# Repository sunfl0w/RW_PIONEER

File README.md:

# RW-Pioneer

RW-Pioneer is a computer project inspired by Ben Eater's [8-bit breadboard computer project](https://www.youtube.com/playlist?list=PLowKtXNTBypGqImE405J2565dvjafglHU) over at YouTube.
I always wanted to build my own crappy computer, and the Pioneer was my first such attempt.
The design is not perfect by any means, but it was the best one I could come up with after a few semesters of studying computer science.

**Note that the RW-Pioneer is a few years old by now and I only compiled old schematics, layouts and code for this repository.**
**I recently added a binary compatible Verilog model of the system with Verilator test suite and Vivado project files for the Nexys A7 board.**

## Content

This repository contains the following schematics and software components:

- RW-Pioneer schematics, paper explaining the architecture and KiCad design files (Schematic and RW_PIONEER_WHITEPAPER.pdf)
- RW-Pioneer Verilog model with Verilator test suite and Vivado project files for the NEXYS A7 board (VerilogModel)
- HEX-Module and 1602-Module schematics and KiCad design files (ExpansionModules)
- Instruction LUT generator for the instruction decoder memory IC of the system (InstructionLUTGenerator)
- Memory-Programmer host and programmer software sources, schematics and KiCad design files (MemoryProgrammer)
- Simple software emulator for the system (RWEMU)

## Licenses

The software and schematics are licensed under the permissive BSD 3-Clause License.

## Links

[Visit my personal website to see the Pioneer in action.](https://www.rechenwerke.com/projects/rw_pioneer)

## Gallery

Image of a prototype board I assembled a few years ago.

Image of the NEXYS A7 board running the RW-Pioneer Verilog model.

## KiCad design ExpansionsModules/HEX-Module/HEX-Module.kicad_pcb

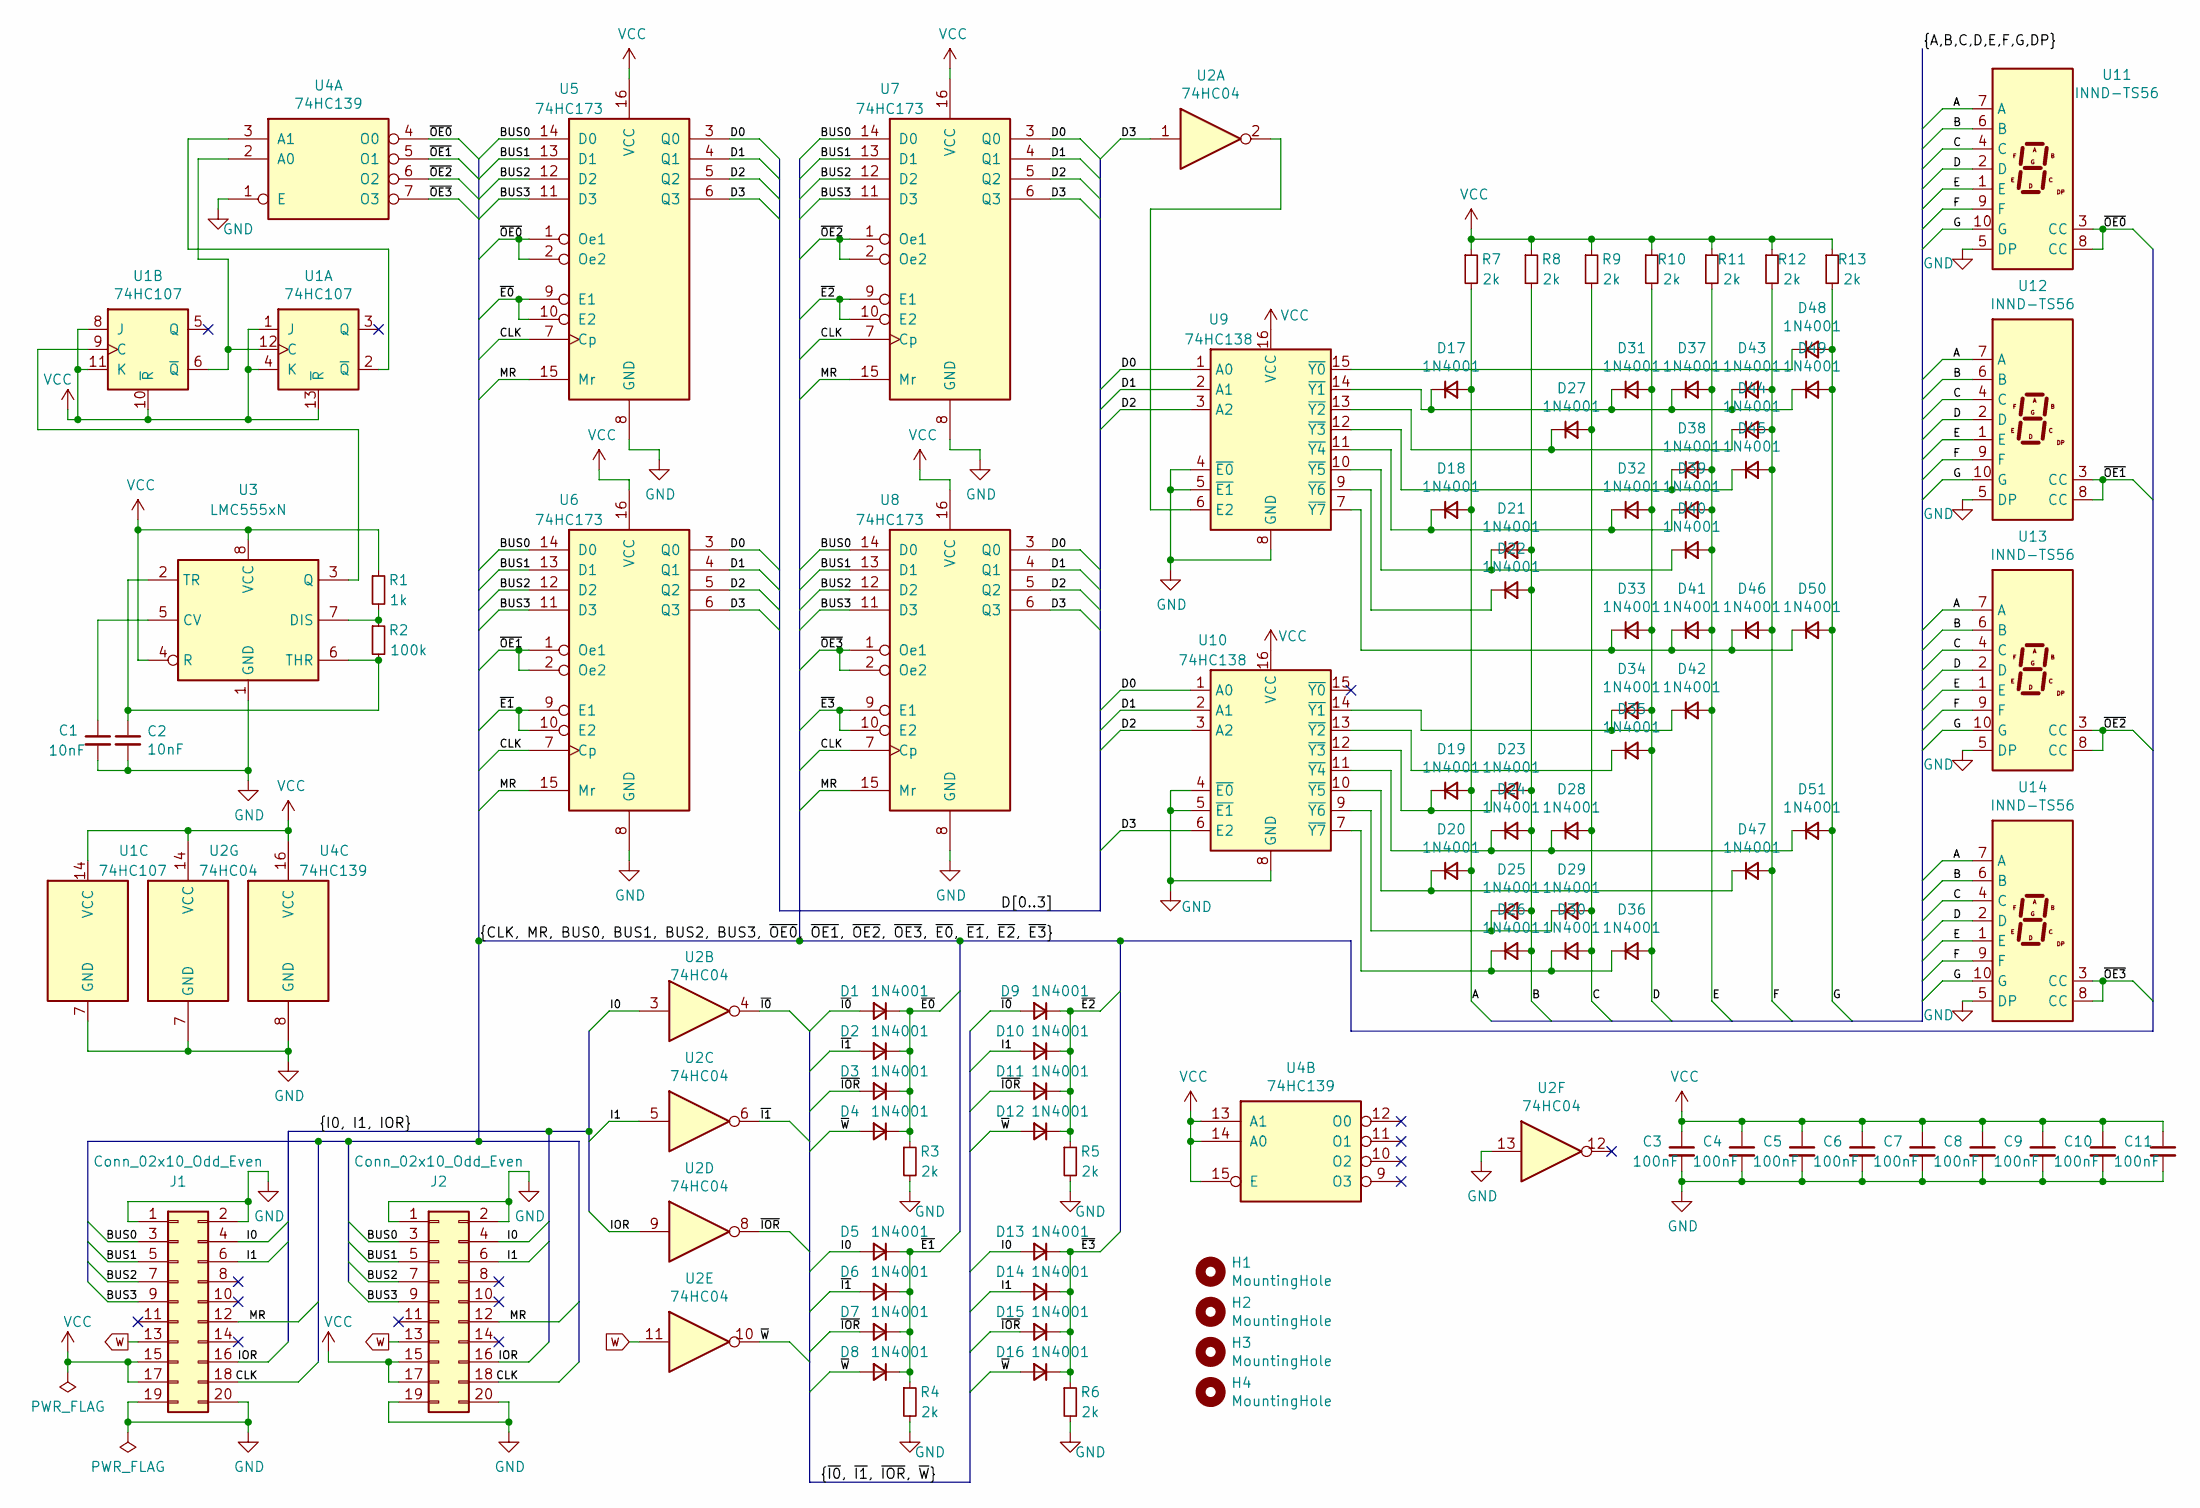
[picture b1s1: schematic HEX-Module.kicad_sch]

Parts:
C1, C2: 10nF; C_Disc_D4.3mm_W1.9mm_P5.00mm
C3, C4, C5, C6, C7, C8, C9, C10, C11: 100nF; C_Disc_D4.3mm_W1.9mm_P5.00mm
D1, D2, D3, D4, D5, D6, D7, D8, D9, D10, D11, D12, D13, D14, D15, D16, D17, D18, D19, D20, D21, D22, D23, D24, D25, D26, D27, D28, D29, D30, D31, D32, D33, D34, D35, D36, D37, D38, D39, D40, D41, D42, D43, D44, D45, D46, D47, D48, D49, D50, D51: 1N4001; D_DO-41_SOD81_P10.16mm_Horizontal
H1, H2, H3, H4: MountingHole; MountingHole_3.2mm_M3
J1: Conn_02x10_Odd_Even; PinSocket_2x10_P2.54mm_Horizontal
J2: Conn_02x10_Odd_Even; IDC-Header_2x10_P2.54mm_Horizontal
R1: 1k; R_Axial_DIN0207_L6.3mm_D2.5mm_P10.16mm_Horizontal
R2: 100k; R_Axial_DIN0207_L6.3mm_D2.5mm_P10.16mm_Horizontal
R3, R4, R5, R6, R7, R8, R9, R10, R11, R12, R13: 2k; R_Axial_DIN0207_L6.3mm_D2.5mm_P10.16mm_Horizontal
U1: 74HC107; DIP-14_W7.62mm
U2: 74HC04; DIP-14_W7.62mm
U3: LMC555xN; DIP-8_W7.62mm
U4: 74HC139; DIP-16_W7.62mm
U5, U6, U7, U8: 74HC173; DIP-16_W7.62mm
U9, U10: 74HC138; DIP-16_W7.62mm
U11, U12, U13, U14: INND-TS56

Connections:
/A: D17.2 (A), D18.2 (A), D19.2 (A), D20.2 (A), R7.2, U11.7 (A), U12.7 (A), U13.7 (A), U14.7 (A)
/B: D21.2 (A), D22.2 (A), D23.2 (A), D24.2 (A), D25.2 (A), D26.2 (A), R8.2, U11.6 (B), U12.6 (B), U13.6 (B), U14.6 (B)
/BUS0: J1.3, J2.3, U5.14 (D0), U6.14 (D0), U7.14 (D0), U8.14 (D0)
/BUS1: J1.5, J2.5, U5.13 (D1), U6.13 (D1), U7.13 (D1), U8.13 (D1)
/BUS2: J1.7, J2.7, U5.12 (D2), U6.12 (D2), U7.12 (D2), U8.12 (D2)
/BUS3: J1.9, J2.9, U5.11 (D3), U6.11 (D3), U7.11 (D3), U8.11 (D3)
/C: D27.2 (A), D28.2 (A), D29.2 (A), D30.2 (A), R9.2, U11.4 (C), U12.4 (C), U13.4 (C), U14.4 (C)
/CLK: J1.18, J2.18, U5.7 (Cp), U6.7 (Cp), U7.7 (Cp), U8.7 (Cp)
/D: D31.2 (A), D32.2 (A), D33.2 (A), D34.2 (A), D35.2 (A), D36.2 (A), R10.2, U11.2 (D), U12.2 (D), U13.2 (D), U14.2 (D)
/D0: U5.3 (Q0), U6.3 (Q0), U7.3 (Q0), U8.3 (Q0), U9.1 (A0), U10.1 (A0)
/D1: U5.4 (Q1), U6.4 (Q1), U7.4 (Q1), U8.4 (Q1), U9.2 (A1), U10.2 (A1)
/D2: U5.5 (Q2), U6.5 (Q2), U7.5 (Q2), U8.5 (Q2), U9.3 (A2), U10.3 (A2)
/D3: U2.1, U5.6 (Q3), U6.6 (Q3), U7.6 (Q3), U8.6 (Q3), U10.6 (E2)
/E: D37.2 (A), D38.2 (A), D39.2 (A), D40.2 (A), D41.2 (A), D42.2 (A), R11.2, U11.1 (E), U12.1 (E), U13.1 (E), U14.1 (E)
/F: D43.2 (A), D44.2 (A), D45.2 (A), D46.2 (A), D47.2 (A), R12.2, U11.9 (F), U12.9 (F), U13.9 (F), U14.9 (F)
/G: D48.2 (A), D49.2 (A), D50.2 (A), D51.2 (A), R13.2, U11.10 (G), U12.10 (G), U13.10 (G), U14.10 (G)
/I0: D5.2 (A), D13.2 (A), J1.4, J2.4, U2.3
/I1: D10.2 (A), D14.2 (A), J1.6, J2.6, U2.5
/IOR: J1.16, J2.16, U2.9
/MR: J1.12, J2.12, U5.15 (Mr), U6.15 (Mr), U7.15 (Mr), U8.15 (Mr)
/~E0: D1.1 (K), D2.1 (K), D3.1 (K), D4.1 (K), R3.1, U5.9 (E1), U5.10 (E2)
/~E1: D5.1 (K), D6.1 (K), D7.1 (K), D8.1 (K), R4.1, U6.9 (E1), U6.10 (E2)
/~E2: D9.1 (K), D10.1 (K), D11.1 (K), D12.1 (K), R5.1, U7.9 (E1), U7.10 (E2)
/~E3: D13.1 (K), D14.1 (K), D15.1 (K), D16.1 (K), R6.1, U8.9 (E1), U8.10 (E2)
/~I0: D1.2 (A), D9.2 (A), U2.4
/~I1: D2.2 (A), D6.2 (A), U2.6
/~IOR: D3.2 (A), D7.2 (A), D11.2 (A), D15.2 (A), U2.8
/~OE0: U4.4 (O0), U5.1 (Oe1), U5.2 (Oe2), U11.3 (CC), U11.8 (CC)
/~OE1: U4.5 (O1), U6.1 (Oe1), U6.2 (Oe2), U12.3 (CC), U12.8 (CC)
/~OE2: U4.6 (O2), U7.1 (Oe1), U7.2 (Oe2), U13.3 (CC), U13.8 (CC)
/~OE3: U4.7 (O3), U8.1 (Oe1), U8.2 (Oe2), U14.3 (CC), U14.8 (CC)
/~W: D4.2 (A), D8.2 (A), D12.2 (A), D16.2 (A), U2.10
GND: C1.2, C2.2, C3.2, C4.2, C5.2, C6.2, C7.2, C8.2, C9.2, C10.2, C11.2, J1.1, J1.2, J1.19, J1.20, J2.1, J2.2, J2.19, J2.20, R3.2, R4.2, R5.2, R6.2, U1.7 (GND), U2.7 (GND), U2.13, U3.1 (GND), U4.1 (E), U4.8 (GND), U5.8 (GND), U6.8 (GND), U7.8 (GND), U8.8 (GND), U9.4 (~E0), U9.5 (~E1), U9.8 (GND), U10.4 (~E0), U10.5 (~E1), U10.8 (GND), U11.5 (DP), U12.5 (DP), U13.5 (DP), U14.5 (DP)
unnamed: D17.1 (K), D31.1 (K), D37.1 (K), D43.1 (K), D49.1 (K), U9.14 (~Y1)
unnamed: D18.1 (K), D32.1 (K), D39.1 (K), U9.11 (~Y4)
unnamed: D19.1 (K), D23.1 (K), U10.12 (~Y3)
unnamed: D20.1 (K), D47.1 (K), U10.10 (~Y5)
unnamed: D21.1 (K), D40.1 (K), U9.10 (~Y5)
unnamed: D22.1 (K), U9.9 (~Y6)
unnamed: D24.1 (K), D28.1 (K), D51.1 (K), U10.11 (~Y4)
unnamed: D25.1 (K), D29.1 (K), U10.9 (~Y6)
unnamed: D26.1 (K), D30.1 (K), D36.1 (K), U10.7 (~Y7)
unnamed: D27.1 (K), D44.1 (K), U9.13 (~Y2)
unnamed: D33.1 (K), D41.1 (K), D46.1 (K), D50.1 (K), U9.7 (~Y7)
unnamed: D34.1 (K), D42.1 (K), U10.14 (~Y1)
unnamed: D35.1 (K), U10.13 (~Y2)
unnamed: D38.1 (K), D45.1 (K), U9.12 (~Y3)
unnamed: D48.1 (K), U9.15 (~Y0)
unnamed: U1.6 (~Q), U1.12 (C), U4.2 (A0)
unnamed: U1.2 (~Q), U4.3 (A1)
unnamed: U1.9 (C), U3.3 (Q)
unnamed: C1.1, U3.5 (CV)
unnamed: R1.2, R2.1, U3.7 (DIS)
unnamed: C2.1, R2.2, U3.2 (TR), U3.6 (THR)
unnamed: U2.2, U9.6 (E2)
VCC: C3.1, C4.1, C5.1, C6.1, C7.1, C8.1, C9.1, C10.1, C11.1, J1.15, J1.17, J2.15, J2.17, R1.1, R7.1, R8.1, R9.1, R10.1, R11.1, R12.1, R13.1, U1.1 (J), U1.4 (K), U1.8 (J), U1.10 (~R), U1.11 (K), U1.13 (~R), U1.14 (VCC), U2.14 (VCC), U3.4 (R), U3.8 (VCC), U4.13 (A1), U4.14 (A0), U4.15 (E), U4.16 (VCC), U5.16 (VCC), U6.16 (VCC), U7.16 (VCC), U8.16 (VCC), U9.16 (VCC), U10.16 (VCC)
W: J1.13, J2.13, U2.11

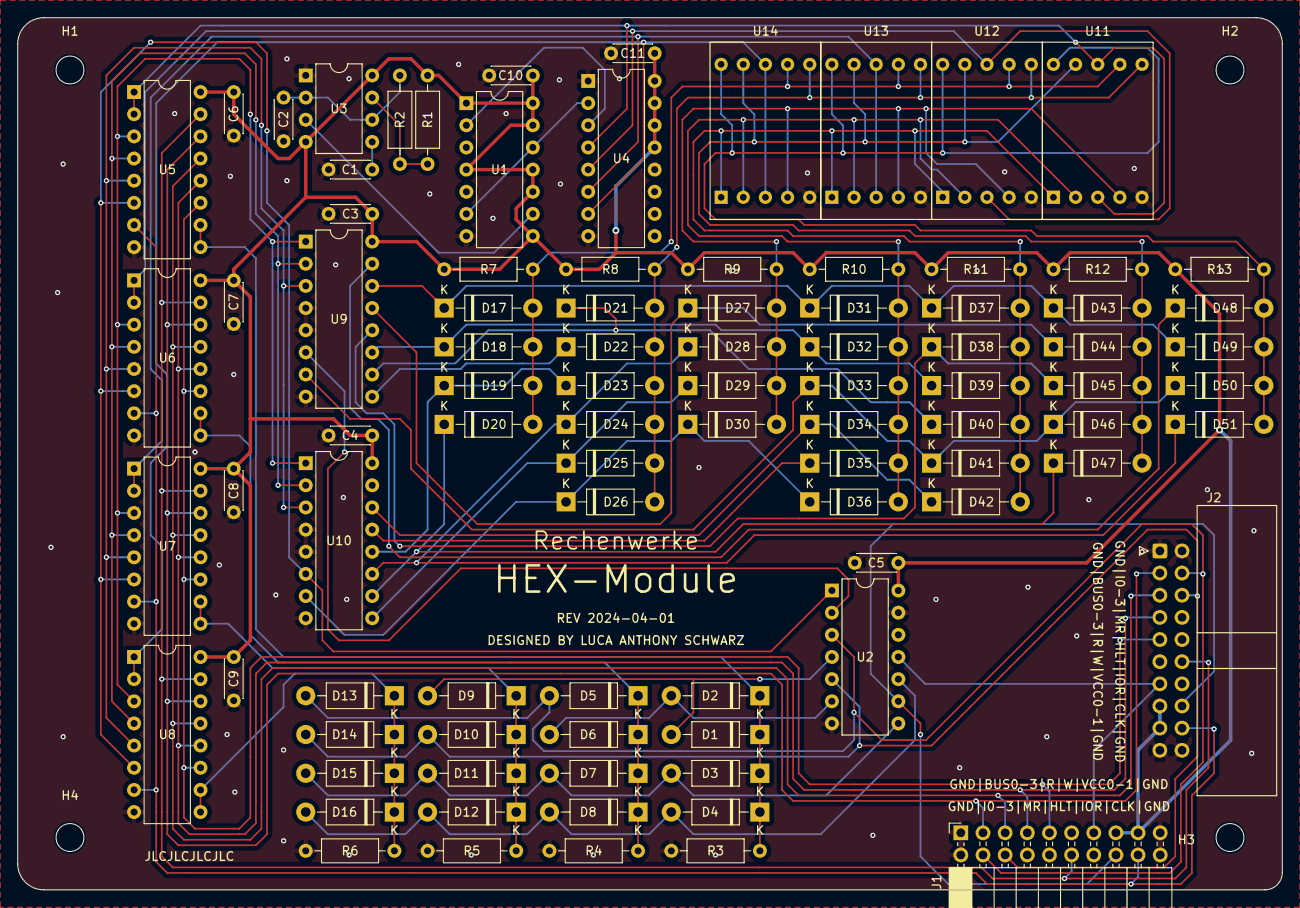
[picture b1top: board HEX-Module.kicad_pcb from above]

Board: 2 copper layers, 145.0 x 100.0 mm, 95 parts (0 on the bottom side), 57 nets.

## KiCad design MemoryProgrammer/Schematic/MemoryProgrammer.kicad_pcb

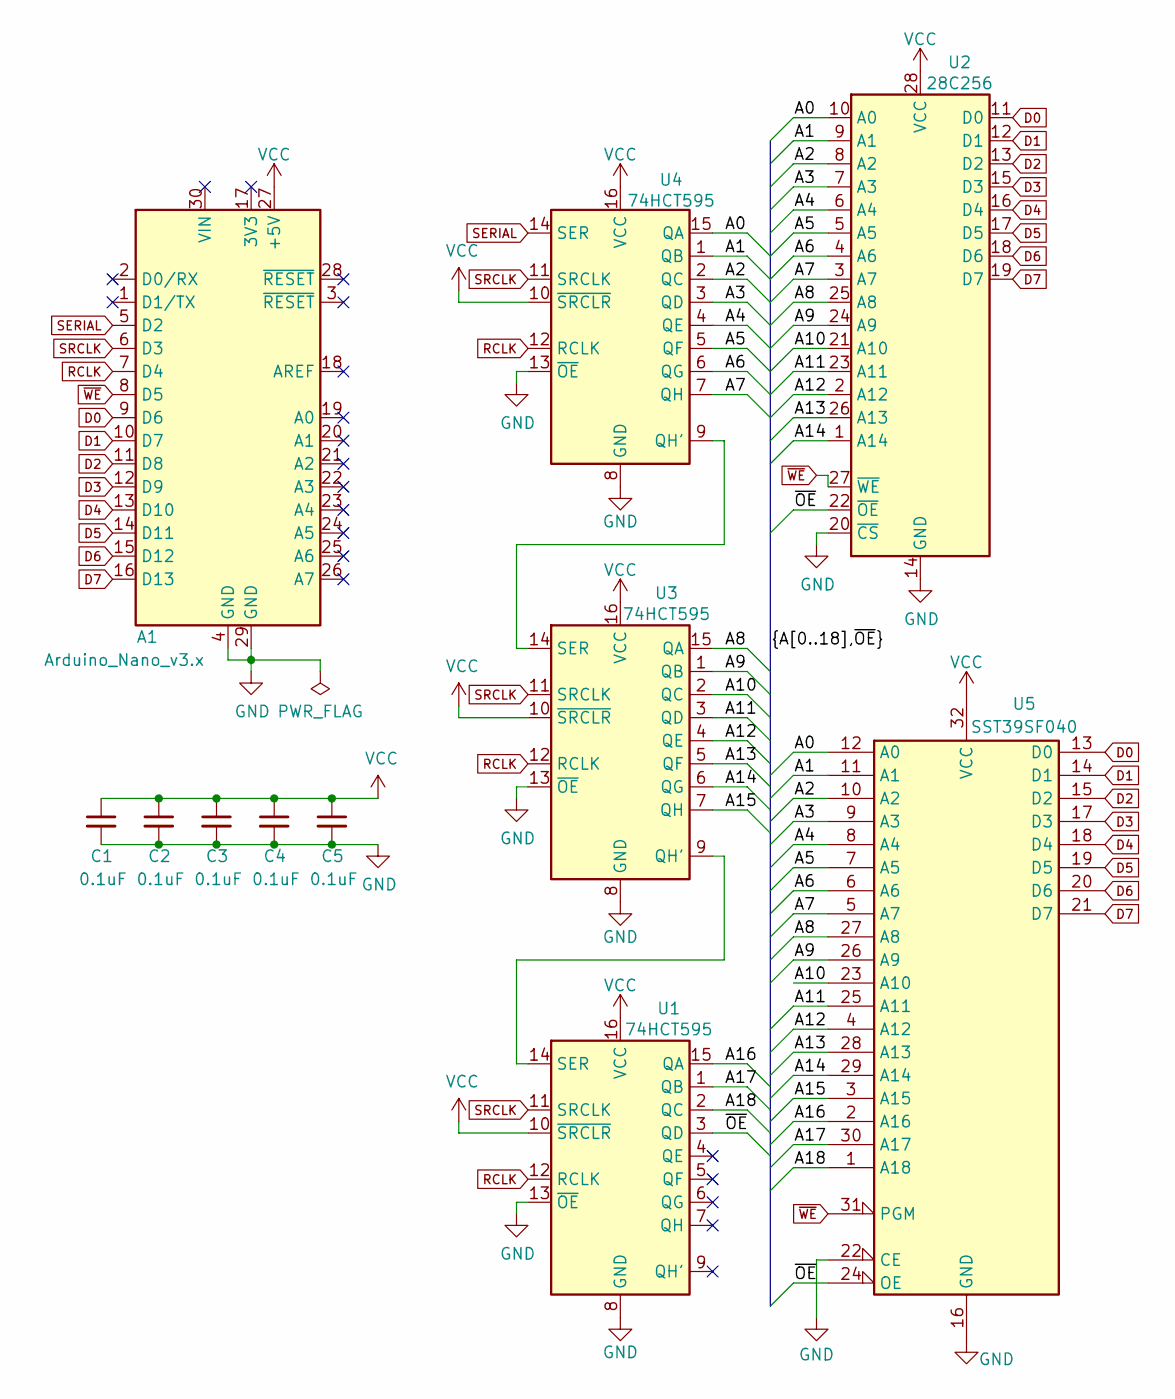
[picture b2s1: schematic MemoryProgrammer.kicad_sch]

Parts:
A1: Arduino_Nano_v3.x; Arduino_Nano
C1, C2, C3, C4, C5: 0.1uF; C_Disc_D4.3mm_W1.9mm_P5.00mm
U1, U3, U4: 74HCT595; DIP-16_W7.62mm
U2: 28C256; DIP-28_W15.24mm_Socket
U5: SST39SF040; DIP-32_W15.24mm_Socket

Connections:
/A0: U2.10 (A0), U4.15 (QA), U5.12 (A0)
/A1: U2.9 (A1), U4.1 (QB), U5.11 (A1)
/A2: U2.8 (A2), U4.2 (QC), U5.10 (A2)
/A3: U2.7 (A3), U4.3 (QD), U5.9 (A3)
/A4: U2.6 (A4), U4.4 (QE), U5.8 (A4)
/A5: U2.5 (A5), U4.5 (QF), U5.7 (A5)
/A6: U2.4 (A6), U4.6 (QG), U5.6 (A6)
/A7: U2.3 (A7), U4.7 (QH), U5.5 (A7)
/A8: U2.25 (A8), U3.15 (QA), U5.27 (A8)
/A9: U2.24 (A9), U3.1 (QB), U5.26 (A9)
/A10: U2.21 (A10), U3.2 (QC), U5.23 (A10)
/A11: U2.23 (A11), U3.3 (QD), U5.25 (A11)
/A12: U2.2 (A12), U3.4 (QE), U5.4 (A12)
/A13: U2.26 (A13), U3.5 (QF), U5.28 (A13)
/A14: U2.1 (A14), U3.6 (QG), U5.29 (A14)
/A15: U3.7 (QH), U5.3 (A15)
/A16: U1.15 (QA), U5.2 (A16)
/A17: U1.1 (QB), U5.30 (A17)
/A18: U1.2 (QC), U5.1 (A18)
/~OE: U1.3 (QD), U2.22 (~OE), U5.24 (OE)
D0: A1.9 (D6), U2.11 (D0), U5.13 (D0)
D1: A1.10 (D7), U2.12 (D1), U5.14 (D1)
D2: A1.11 (D8), U2.13 (D2), U5.15 (D2)
D3: A1.12 (D9), U2.15 (D3), U5.17 (D3)
D4: A1.13 (D10), U2.16 (D4), U5.18 (D4)
D5: A1.14 (D11), U2.17 (D5), U5.19 (D5)
D6: A1.15 (D12), U2.18 (D6), U5.20 (D6)
D7: A1.16 (D13), U2.19 (D7), U5.21 (D7)
GND: A1.4 (GND), A1.29 (GND), C1.2, C2.2, C3.2, C4.2, C5.2, U1.8 (GND), U1.13 (~OE), U2.14 (GND), U2.20 (~CS), U3.8 (GND), U3.13 (~OE), U4.8 (GND), U4.13 (~OE), U5.16 (GND), U5.22 (CE)
unnamed: U1.14 (SER), U3.9 (QH')
unnamed: U3.14 (SER), U4.9 (QH')
RCLK: A1.7 (D4), U1.12 (RCLK), U3.12 (RCLK), U4.12 (RCLK)
SERIAL: A1.5 (D2), U4.14 (SER)
SRCLK: A1.6 (D3), U1.11 (SRCLK), U3.11 (SRCLK), U4.11 (SRCLK)
VCC: A1.27 (+5V), C1.1, C2.1, C3.1, C4.1, C5.1, U1.10 (~SRCLR), U1.16 (VCC), U2.28 (VCC), U3.10 (~SRCLR), U3.16 (VCC), U4.10 (~SRCLR), U4.16 (VCC), U5.32 (VCC)
~WE: A1.8 (D5), U2.27 (~WE), U5.31 (PGM)

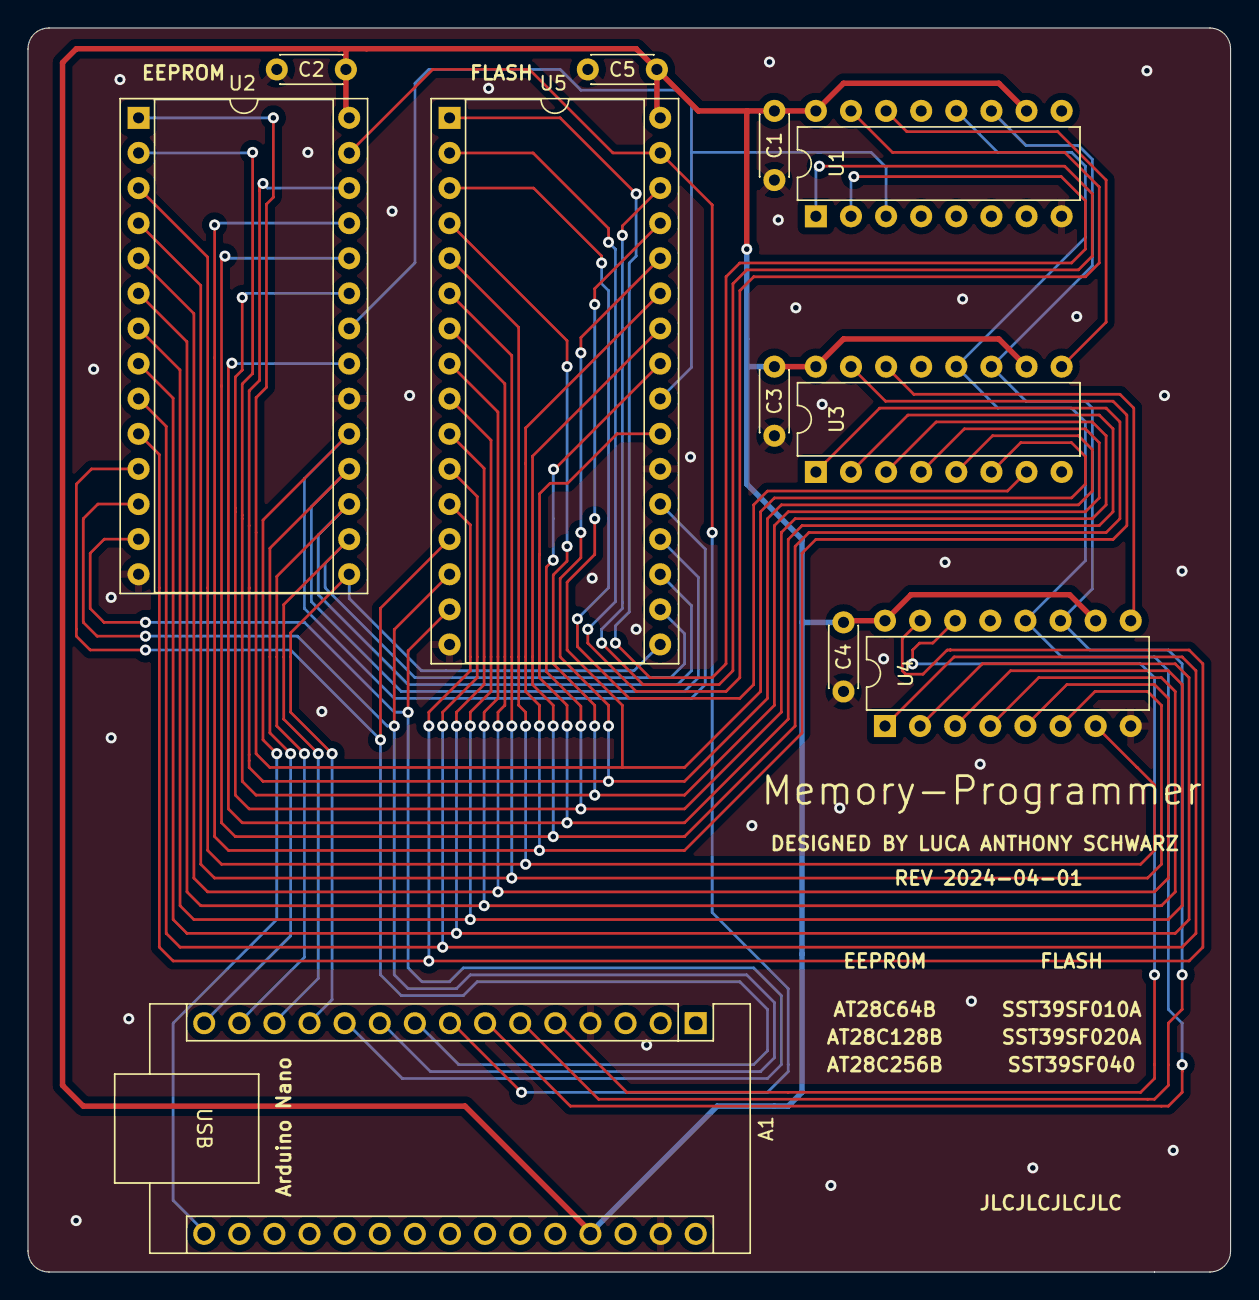
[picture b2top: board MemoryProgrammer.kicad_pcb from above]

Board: 2 copper layers, 87.0 x 90.0 mm, 11 parts (0 on the bottom side), 36 nets.
